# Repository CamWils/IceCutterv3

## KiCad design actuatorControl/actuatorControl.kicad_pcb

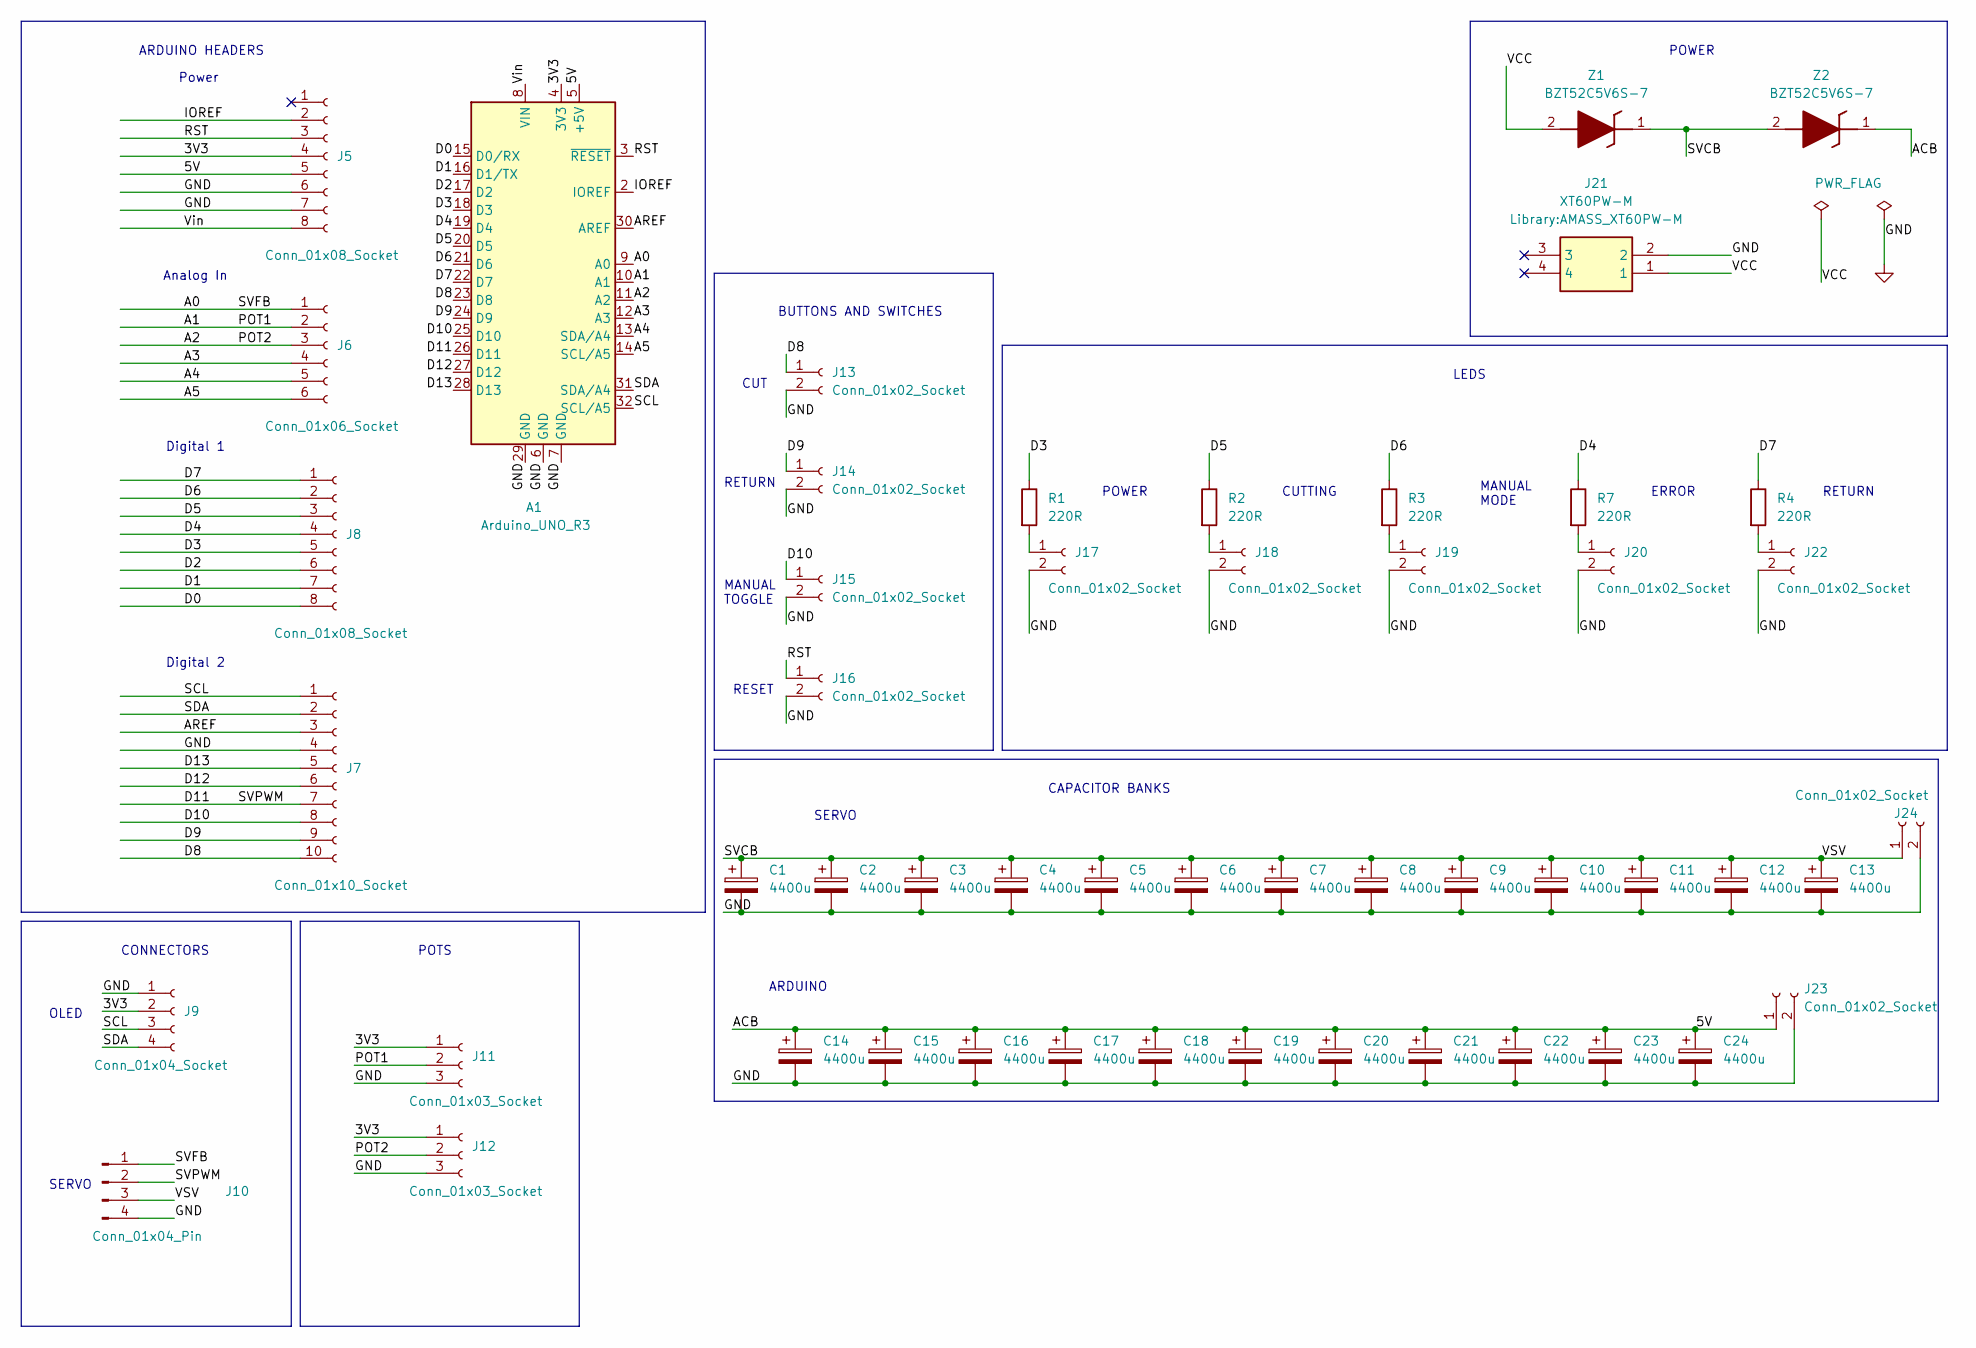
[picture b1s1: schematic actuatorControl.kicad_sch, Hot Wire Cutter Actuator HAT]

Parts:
A1: Arduino_UNO_R3
C1, C2, C3, C4, C5, C6, C7, C8, C9, C10, C11, C12, C13, C14, C15, C16, C17, C18, C19, C20, C21, C22, C23, C24: 4400u; CP_Radial_D16.0mm_P7.50mm
J5, J8: Conn_01x08_Socket; PinSocket_1x08_P2.54mm_Vertical
J6: Conn_01x06_Socket; PinSocket_1x06_P2.54mm_Vertical
J7: Conn_01x10_Socket; PinSocket_1x10_P2.54mm_Vertical
J9: Conn_01x04_Socket; PinSocket_1x04_P2.54mm_Vertical
J10: Conn_01x04_Pin; PinHeader_1x04_P2.54mm_Vertical
J11, J12: Conn_01x03_Socket; PinSocket_1x03_P2.54mm_Vertical
J13, J14, J15, J16, J17, J18, J19, J20, J22, J23, J24: Conn_01x02_Socket; PinSocket_1x02_P2.54mm_Vertical
J21: XT60PW-M; AMASS_XT60PW-M; Manufacturer_Part_Number XT60PW-M; LCSC C98732
R1, R2, R3, R4, R7: 220R; R_Axial_DIN0207_L6.3mm_D2.5mm_P7.62mm_Horizontal
Z1, Z2: BZT52C5V6S-7; SOD2513X105N; Manufacturer_Part_Number BZT52C5V6S-7; Mouser Part Number 621-BZT52C5V6S

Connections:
/3V3: A1.4 (3V3), J5.4, J9.2, J11.1, J12.1
/5V: A1.5 (+5V), C14.1, C15.1, C16.1, C17.1, C18.1, C19.1, C20.1, C21.1, C22.1, C23.1, C24.1, J5.5, J23.1, Z2.1 (K)
/A0: A1.9 (A0), J6.1, J10.1
/A1: A1.10 (A1), J6.2, J11.2
/A2: A1.11 (A2), J6.3, J12.2
/A3: A1.12 (A3), J6.4
/A4: A1.13 (SDA/A4), J6.5
/A5: A1.14 (SCL/A5), J6.6
/AREF: A1.30 (AREF), J7.3
/D0: A1.15 (D0/RX), J8.8
/D1: A1.16 (D1/TX), J8.7
/D2: A1.17 (D2), J8.6
/D3: A1.18 (D3), J8.5, R1.1
/D4: A1.19 (D4), J8.4, R7.1
/D5: A1.20 (D5), J8.3, R2.1
/D6: A1.21 (D6), J8.2, R3.1
/D7: A1.22 (D7), J8.1, R4.1
/D8: A1.23 (D8), J7.10, J13.1
/D9: A1.24 (D9), J7.9, J14.1
/D10: A1.25 (D10), J7.8, J15.1
/D11: A1.26 (D11), J7.7, J10.2
/D12: A1.27 (D12), J7.6
/D13: A1.28 (D13), J7.5
/IOREF: A1.2 (IOREF), J5.2
/RST: A1.3 (~RESET), J5.3, J16.1
/SCL: A1.32 (SCL/A5), J7.1, J9.3
/SDA: A1.31 (SDA/A4), J7.2, J9.4
/SVCB: C1.1, C2.1, C3.1, C4.1, C5.1, C6.1, C7.1, C8.1, C9.1, C10.1, C11.1, C12.1, C13.1, J10.3, J24.1, Z1.1 (K), Z2.2 (A)
/VCC: J21.1, Z1.2 (A)
/Vin: A1.8 (VIN), J5.8
GND: A1.6 (GND), A1.7 (GND), A1.29 (GND), C1.2, C2.2, C3.2, C4.2, C5.2, C6.2, C7.2, C8.2, C9.2, C10.2, C11.2, C12.2, C13.2, C14.2, C15.2, C16.2, C17.2, C18.2, C19.2, C20.2, C21.2, C22.2, C23.2, C24.2, J5.6, J5.7, J7.4, J9.1, J10.4, J11.3, J12.3, J13.2, J14.2, J15.2, J16.2, J17.2, J18.2, J19.2, J20.2, J21.2, J22.2, J23.2, J24.2
unnamed: J17.1, R1.2
unnamed: J18.1, R2.2
unnamed: J19.1, R3.2
unnamed: J20.1, R7.2
unnamed: J22.1, R4.2

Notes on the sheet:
CAPACITOR BANKS
RESET
Analog In
ERROR
Digital 2
SERVO
BUTTONS AND SWITCHES
MANUAL MODE
POWER
ARDUINO
CUTTING
Power
CUT
CONNECTORS
RETURN
Digital 1
MANUAL TOGGLE
OLED
RETURN
ARDUINO HEADERS
POTS
LEDS

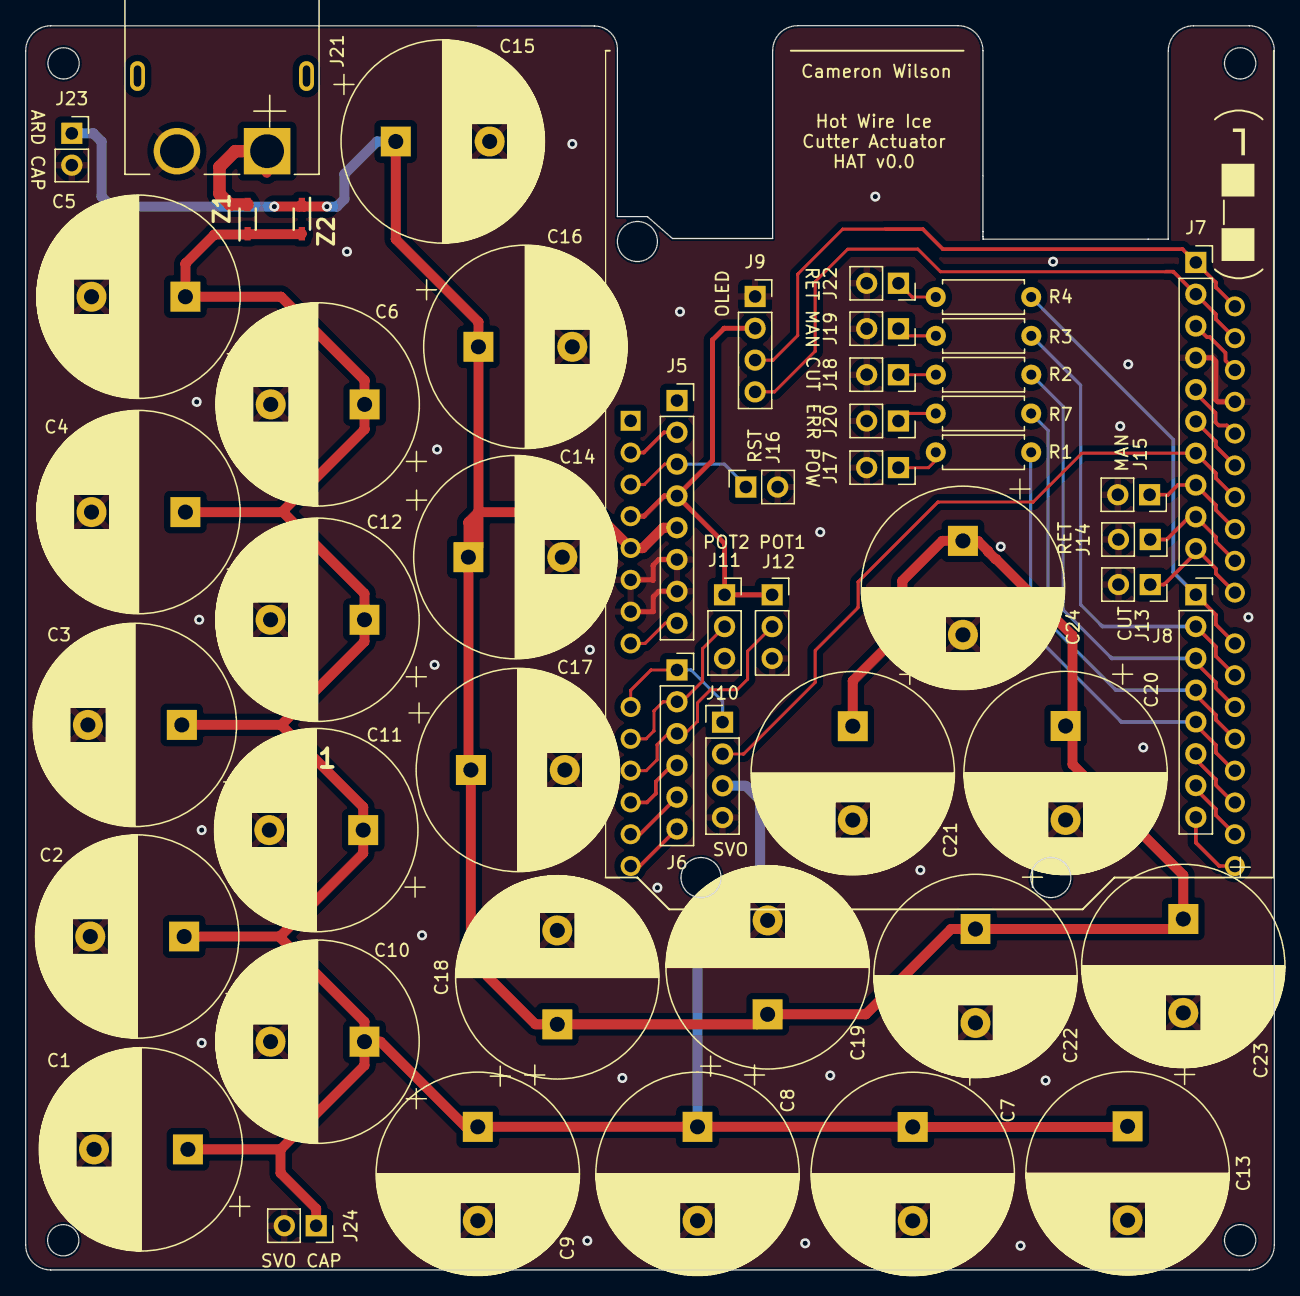
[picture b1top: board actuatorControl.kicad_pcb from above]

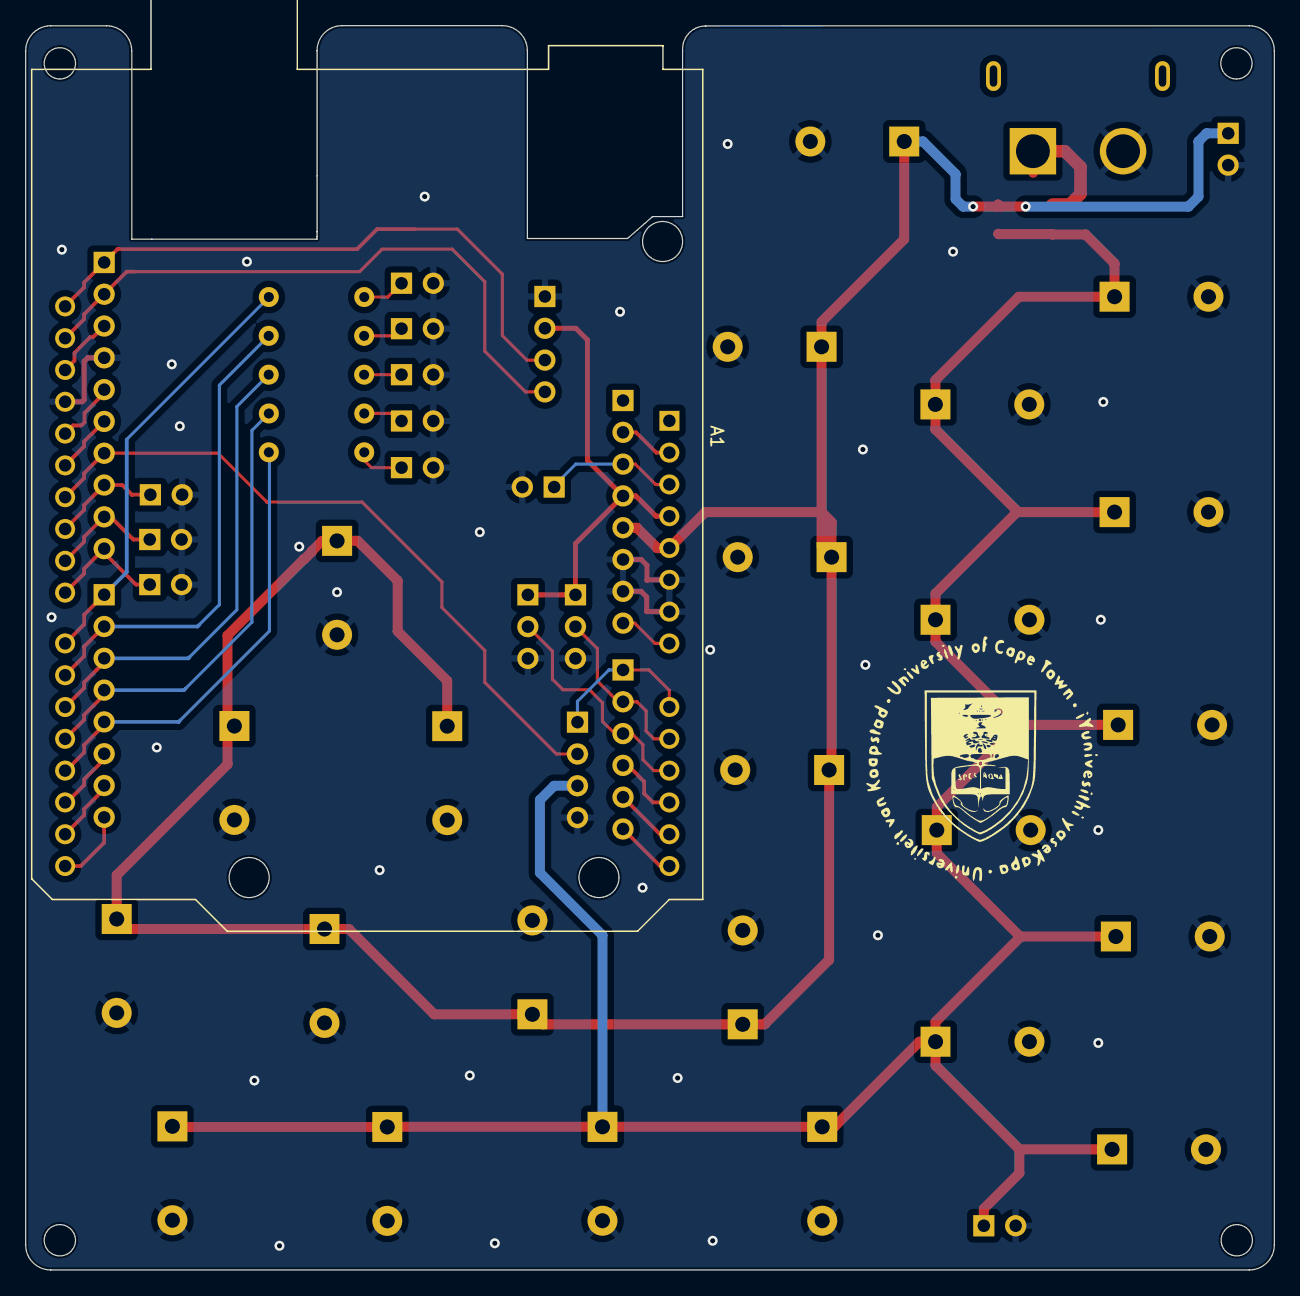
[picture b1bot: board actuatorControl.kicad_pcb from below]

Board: 2 copper layers, 99.7 x 99.4 mm, 53 parts (2 on the bottom side), 36 nets.

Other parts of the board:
G1: LOGO

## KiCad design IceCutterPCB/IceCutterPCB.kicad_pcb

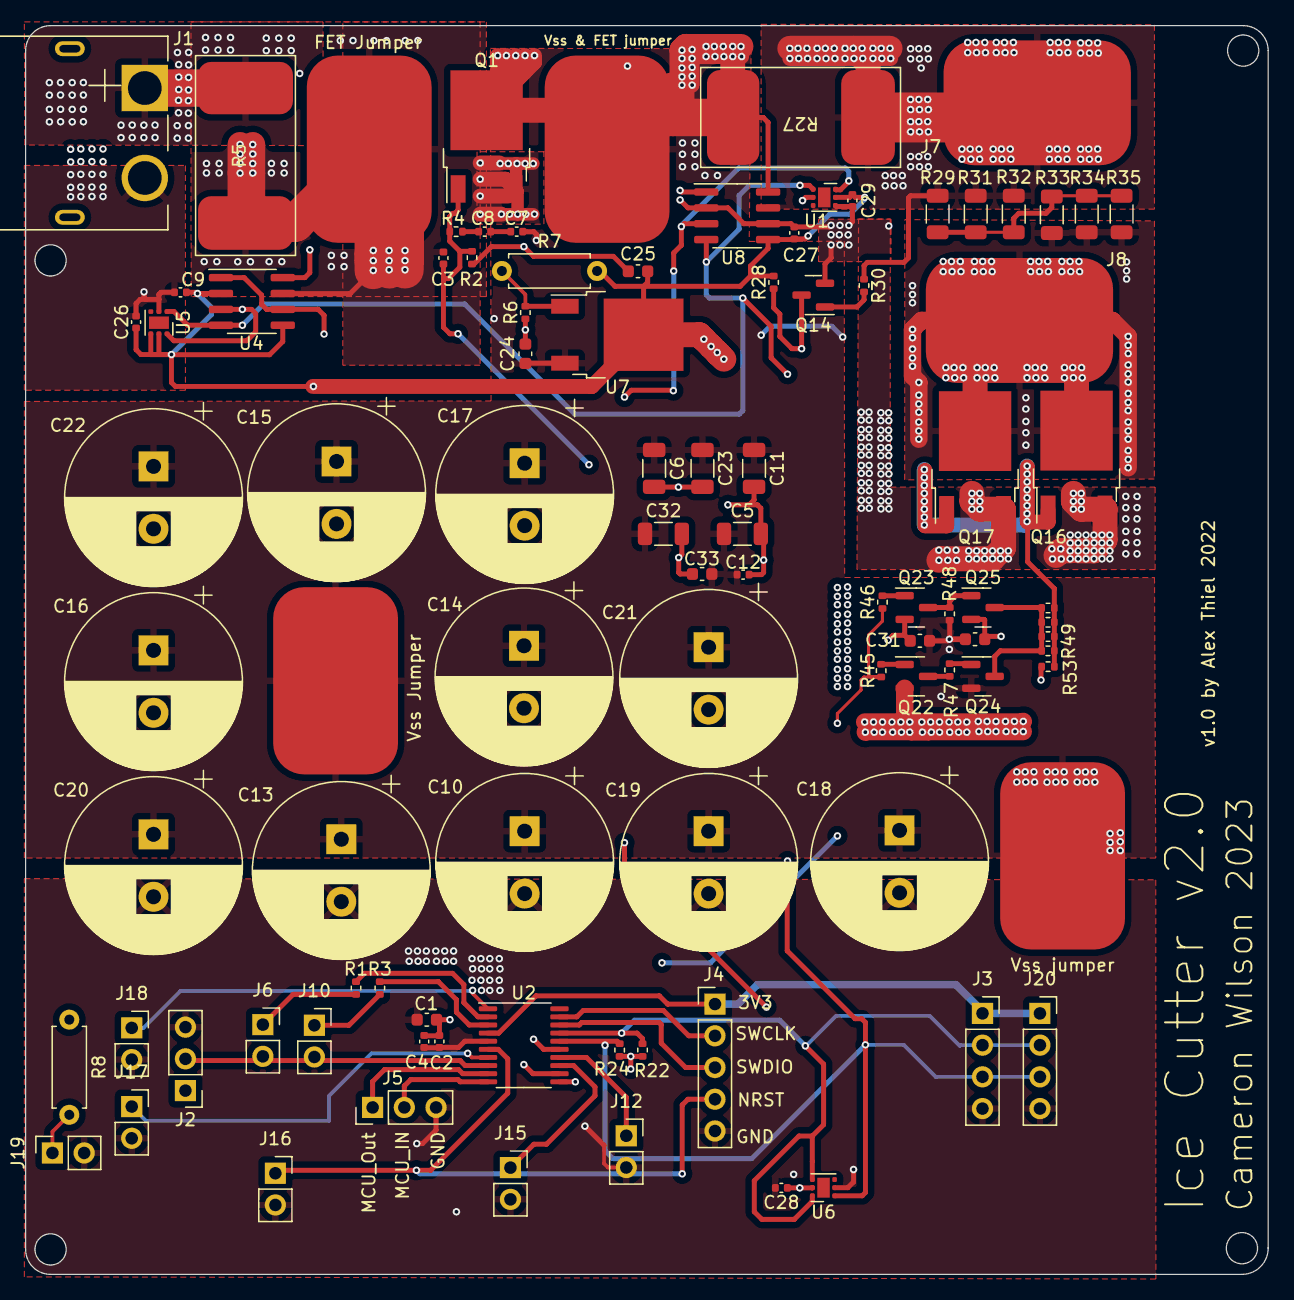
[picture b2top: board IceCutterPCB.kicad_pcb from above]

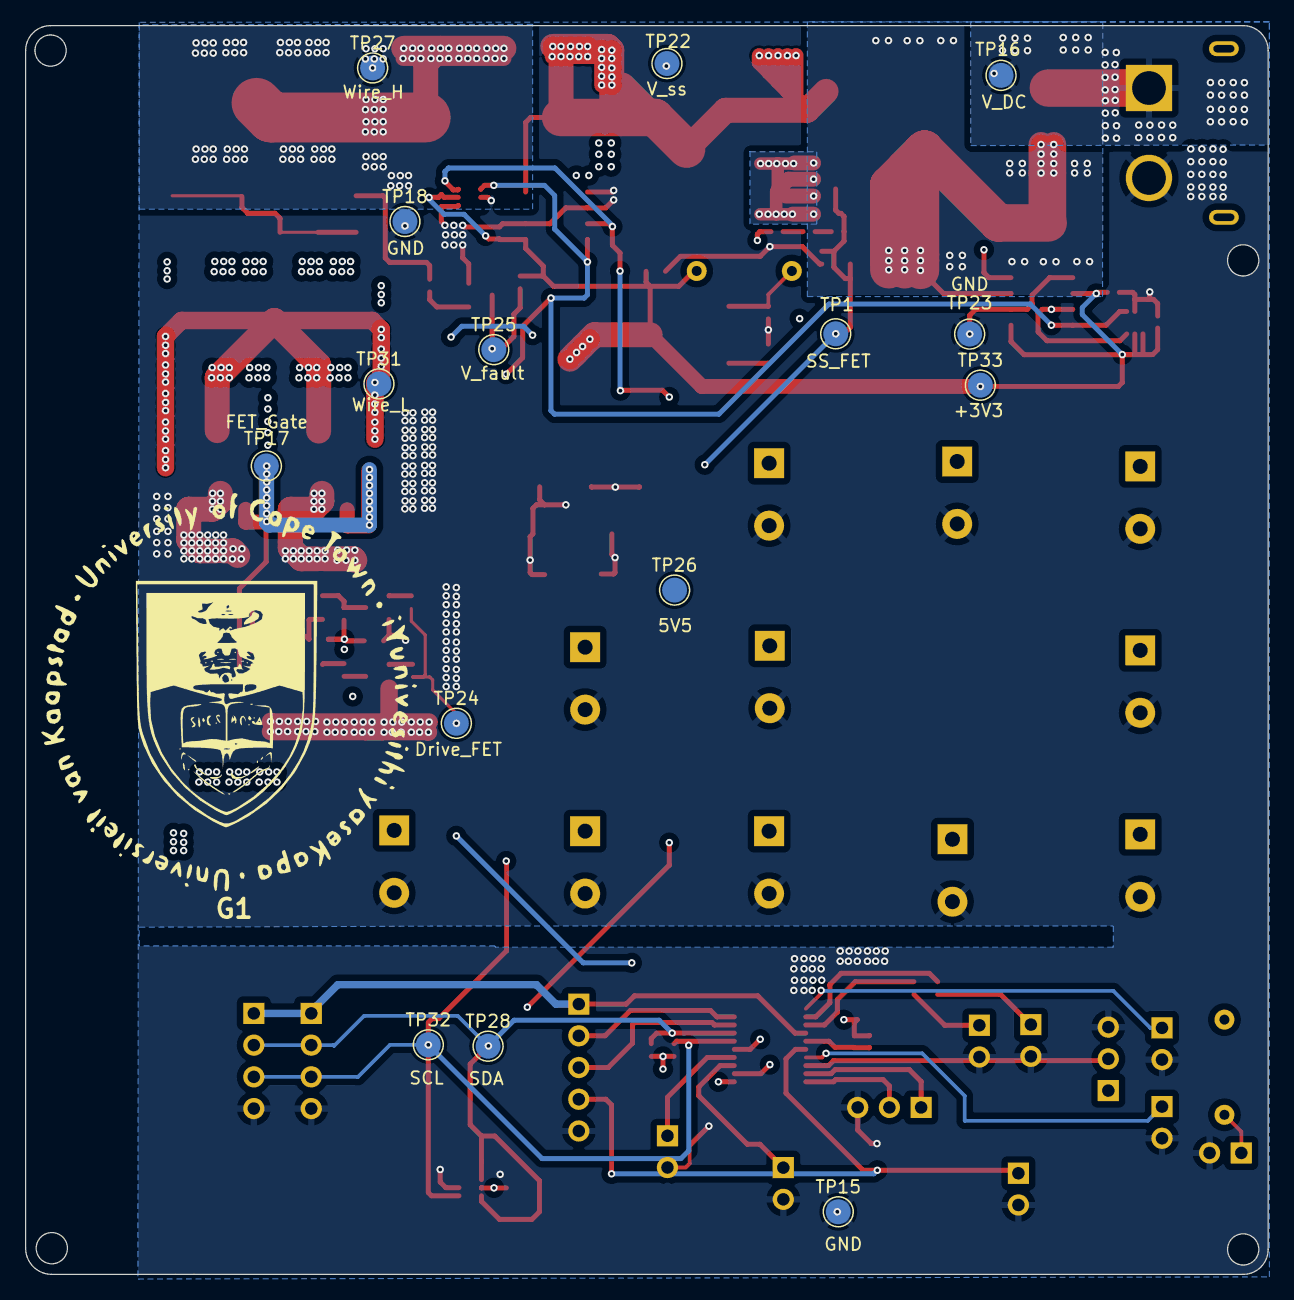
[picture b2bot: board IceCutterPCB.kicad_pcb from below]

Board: 4 copper layers, 99.5 x 100.0 mm, 112 parts (16 on the bottom side), 39 nets.

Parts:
C1, C24, C25, C30, C31, C33: 10u; C_0603_1608Metric
C2, C3, C4, C7, C8, C9, C12, C26, C27, C28, C29: 100n; C_0402_1005Metric
C5, C6, C11, C23, C32: 100u; C_1206_3216Metric
C10, C13, C14, C15, C16, C17, C18, C19, C20, C21, C22: 4.7m; CP_Radial_D14.0mm_P5.00mm
G1: LOGO
J1: XT60PW-M; AMASS_XT60PW-M
J2: pot; PinHeader_1x03_P2.54mm_Vertical
J3, J20: Conn_01x04_Socket; PinSocket_1x04_P2.54mm_Vertical
J4: program2; PinHeader_1x05_P2.54mm_Vertical
J5: UART; PinHeader_1x03_P2.54mm_Vertical
J6, J10, J12, J15, J16, J17, J18, J19: Conn_01x02_Socket; PinSocket_1x02_P2.54mm_Vertical
J7, J8, J9, J11, J13, J14: Conn_01x01_Male; SMD_Pad_15x10
Q1: Q_PMOS_GDS; TO-252-2
Q14: Q_NMOS_GSD; SOT-23
Q16, Q17: Q_NMOS_GDS; TO-252-2
Q22, Q23, Q25: S8050_SMD; SOT-23
Q24: S8550; SOT-23
R1, R3, R47, R48: 1k5; R_0402_1005Metric
R2, R53: 3.3M; R_0402_1005Metric
R4, R49, R50, R51, R52: 100R; R_0402_1005Metric
R5, R27: 0.75mR; res_5930
R6, R30: 330R; R_0402_1005Metric
R7, R8: 220R; R_Axial_DIN0207_L6.3mm_D2.5mm_P7.62mm_Horizontal
R22, R24, R28, R45, R46: 4k7; R_0402_1005Metric
R29, R31, R32, R33, R34, R35: 100R; R_1206_3216Metric
TP1, TP15, TP16, TP17, TP18, TP22, TP23, TP24, TP25, TP26, TP27, TP28, TP31, TP32, TP33: TestPoint; TestPoint_Pad_D2.0mm
U1, U5, U6: TMP117; WSON-6-1EP_2x2mm_P0.65mm_EP1x1.6mm
U2: STM32G030XX; TSSOP-20_4.4x6.5mm_P0.65mm
U4, U8: INA219AxD; SOIC-8_3.9x4.9mm_P1.27mm
U7: LM317_TO-252; TO-252-2

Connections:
+3V3: C1.1, C2.1, C4.1, C9.1, C25.1, C26.1, C27.1, C28.1, C29.1, J2.1, J3.1, J4.1, J20.1, R7.2, R8.1, R22.2, R24.2, R28.2, TP33.1, U1.5 (V+), U2.4 (VDD), U4.2 (A0), U4.5 (VS), U5.4 (ADD0), U5.5 (V+), U6.5 (V+), U7.2 (VO), U8.5 (VS)
/Drive_FET: R45.1, R46.1, TP24.1, U2.11 (PA4)
/FET_GATE: Q16.1 (G), Q17.1 (G), R49.2, R50.2, R51.2, R52.2, R53.1, TP17.1
/LED1: R1.1, U2.2 (PB9/PC14-OSC32_IN)
/LED2: R3.1, U2.3 (PC15-OSC32_OUT)
/MCU_In: J5.2, U2.10 (PA3)
/MCU_Out: J5.1, U2.9 (PA2)
/NRST: J4.4, J16.1, U2.6 (NRST)
/PB1: J12.1, U2.14 (PA7)
/PB2: J15.1, U2.13 (PA6)
/PB3: J17.1, U2.7 (PA0)
/PB4: J18.1, U2.1 (PB7/PB8)
/SCL: J3.3, J20.3, R24.1, TP32.1, U1.1 (SCL), U2.16 (PA11[PA9]), U4.4 (SCL), U5.1 (SCL), U6.1 (SCL), U8.4 (SCL)
/SDA: J3.2, J20.2, R22.1, TP28.1, U1.6 (SDA), U2.17 (PA12[PA10]), U4.3 (SDA), U5.6 (SDA), U6.4 (ADD0), U6.6 (SDA), U8.3 (SDA)
/SS_FET: C3.2, Q1.1 (G), R2.1, R4.1, TP1.1, U2.15 (PB0/PB1/PB2/PA8)
/SS_in: C3.1, J13.1, Q1.3 (S), R5.2, U4.7 (IN-)
/SWCLK: J4.2, U2.19 (PA15/PA14-BOOT0)
/SWDIO: J4.3, U2.18 (PA13)
/VOUT_FAULT: Q14.3 (D), R28.1, TP25.1, U2.12 (PA5)
/V_SS: C5.1, C6.1, C7.1, C10.1, C11.1, C12.1, C13.1, C14.1, C15.1, C16.1, C17.1, C18.1, C19.1, C20.1, C21.1, C22.1, C23.1, C24.1, C30.1, C31.1, C32.1, C33.1, J9.1, J11.1, J14.1, Q1.2 (D), Q24.2 (E), R27.1, R48.2, TP22.1, U7.3 (VI), U8.8 (IN+)
/Wire_H: J7.1, R27.2, R29.1, R30.1, R31.1, R32.1, TP27.1, U8.7 (IN-)
/Wire_L: J8.1, Q16.2 (D), Q17.2 (D), R33.2, R34.2, R35.2, TP31.1
/pot: J2.2, U2.8 (PA1)
GND: C1.2, C2.2, C4.2, C5.2, C6.2, C9.2, C10.2, C11.2, C12.2, C13.2, C14.2, C15.2, C16.2, C17.2, C18.2, C19.2, C20.2, C21.2, C22.2, C23.2, C24.2, C25.2, C26.2, C27.2, C28.2, C29.2, C30.2, C31.2, C32.2, C33.2, J1.2 (-), J2.3, J3.4, J4.5, J5.3, J6.2, J10.2, J12.2, J15.2, J16.2, J17.2, J18.2, J19.2, J20.4, Q14.2 (S), Q16.3 (S), Q17.3 (S), Q22.2 (E), Q23.2 (E), Q25.2 (E), R2.2, R6.1, R53.2, TP15.1, TP18.1, TP23.1, U1.2 (GND), U1.4 (ADD0), U2.5 (VSS), U4.1 (A1), U4.6 (GND), U5.2 (GND), U6.2 (GND), U8.1 (A1), U8.2 (A0), U8.6 (GND)
unnamed: C7.2, C8.1
unnamed: C8.2, R4.2
unnamed: J6.1, R1.2
unnamed: J10.1, R3.2
unnamed: J19.1, R8.2
unnamed: Q14.1 (G), R30.2
unnamed: Q22.1 (B), R45.2
unnamed: Q22.3 (C), R47.1
unnamed: Q23.1 (B), R46.2
unnamed: Q23.3 (C), Q25.1 (B), R48.1
unnamed: Q24.1 (B), R47.2
unnamed: Q24.3 (C), Q25.3 (C), R49.1, R50.1, R51.1, R52.1
unnamed: R29.2, R31.2, R32.2, R33.1, R34.1, R35.1
unnamed: R6.2, R7.1, U7.1 (ADJ)
VDC: J1.1 (+), R5.1, TP16.1, U4.8 (IN+)
